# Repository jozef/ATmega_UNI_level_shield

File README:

NAME

    ATmega UNI Level Shield - voltage level shifter shield

DESCRIPTION

    Small shield for two digital pins when 5V←→3.3V voltage level shifting
    is needed.

LICENSE

    This is free software & hardware, licensed under the MIT License.

AUTHOR

        Jozef Kutej

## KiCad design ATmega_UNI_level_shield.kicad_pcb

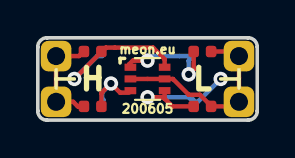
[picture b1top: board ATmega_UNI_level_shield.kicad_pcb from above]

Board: 2 copper layers, 12.2 x 4.6 mm, 8 parts (1 on the bottom side), 6 nets.

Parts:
J5: pins; PinSocket_2x02_P2.54mm_Vertical_SMD_no_lines
J11: low; PinHeader_1x02_P2.54mm_Vertical_no_lines
J12: high; PinHeader_1x02_P2.54mm_Vertical_no_lines
Q1: BSS138PS; SOT-363_SC-70-6_dot
R11, R12, R21, R22: 10k; R_0402_1005Metric

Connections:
D1_H: J5.1, Q1.6, R12.2
D1_L: J5.2, Q1.1, R11.2
D2_H: J5.3, Q1.3, R22.2
D2_L: J5.4, Q1.4, R21.2
VIO_H: J12.1, J12.2, R12.1, R22.1
VIO_L: J11.1, J11.2, Q1.2, Q1.5, R11.1, R21.1

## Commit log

2020-05-13 initial
2020-06-05 bigger H & L letters
